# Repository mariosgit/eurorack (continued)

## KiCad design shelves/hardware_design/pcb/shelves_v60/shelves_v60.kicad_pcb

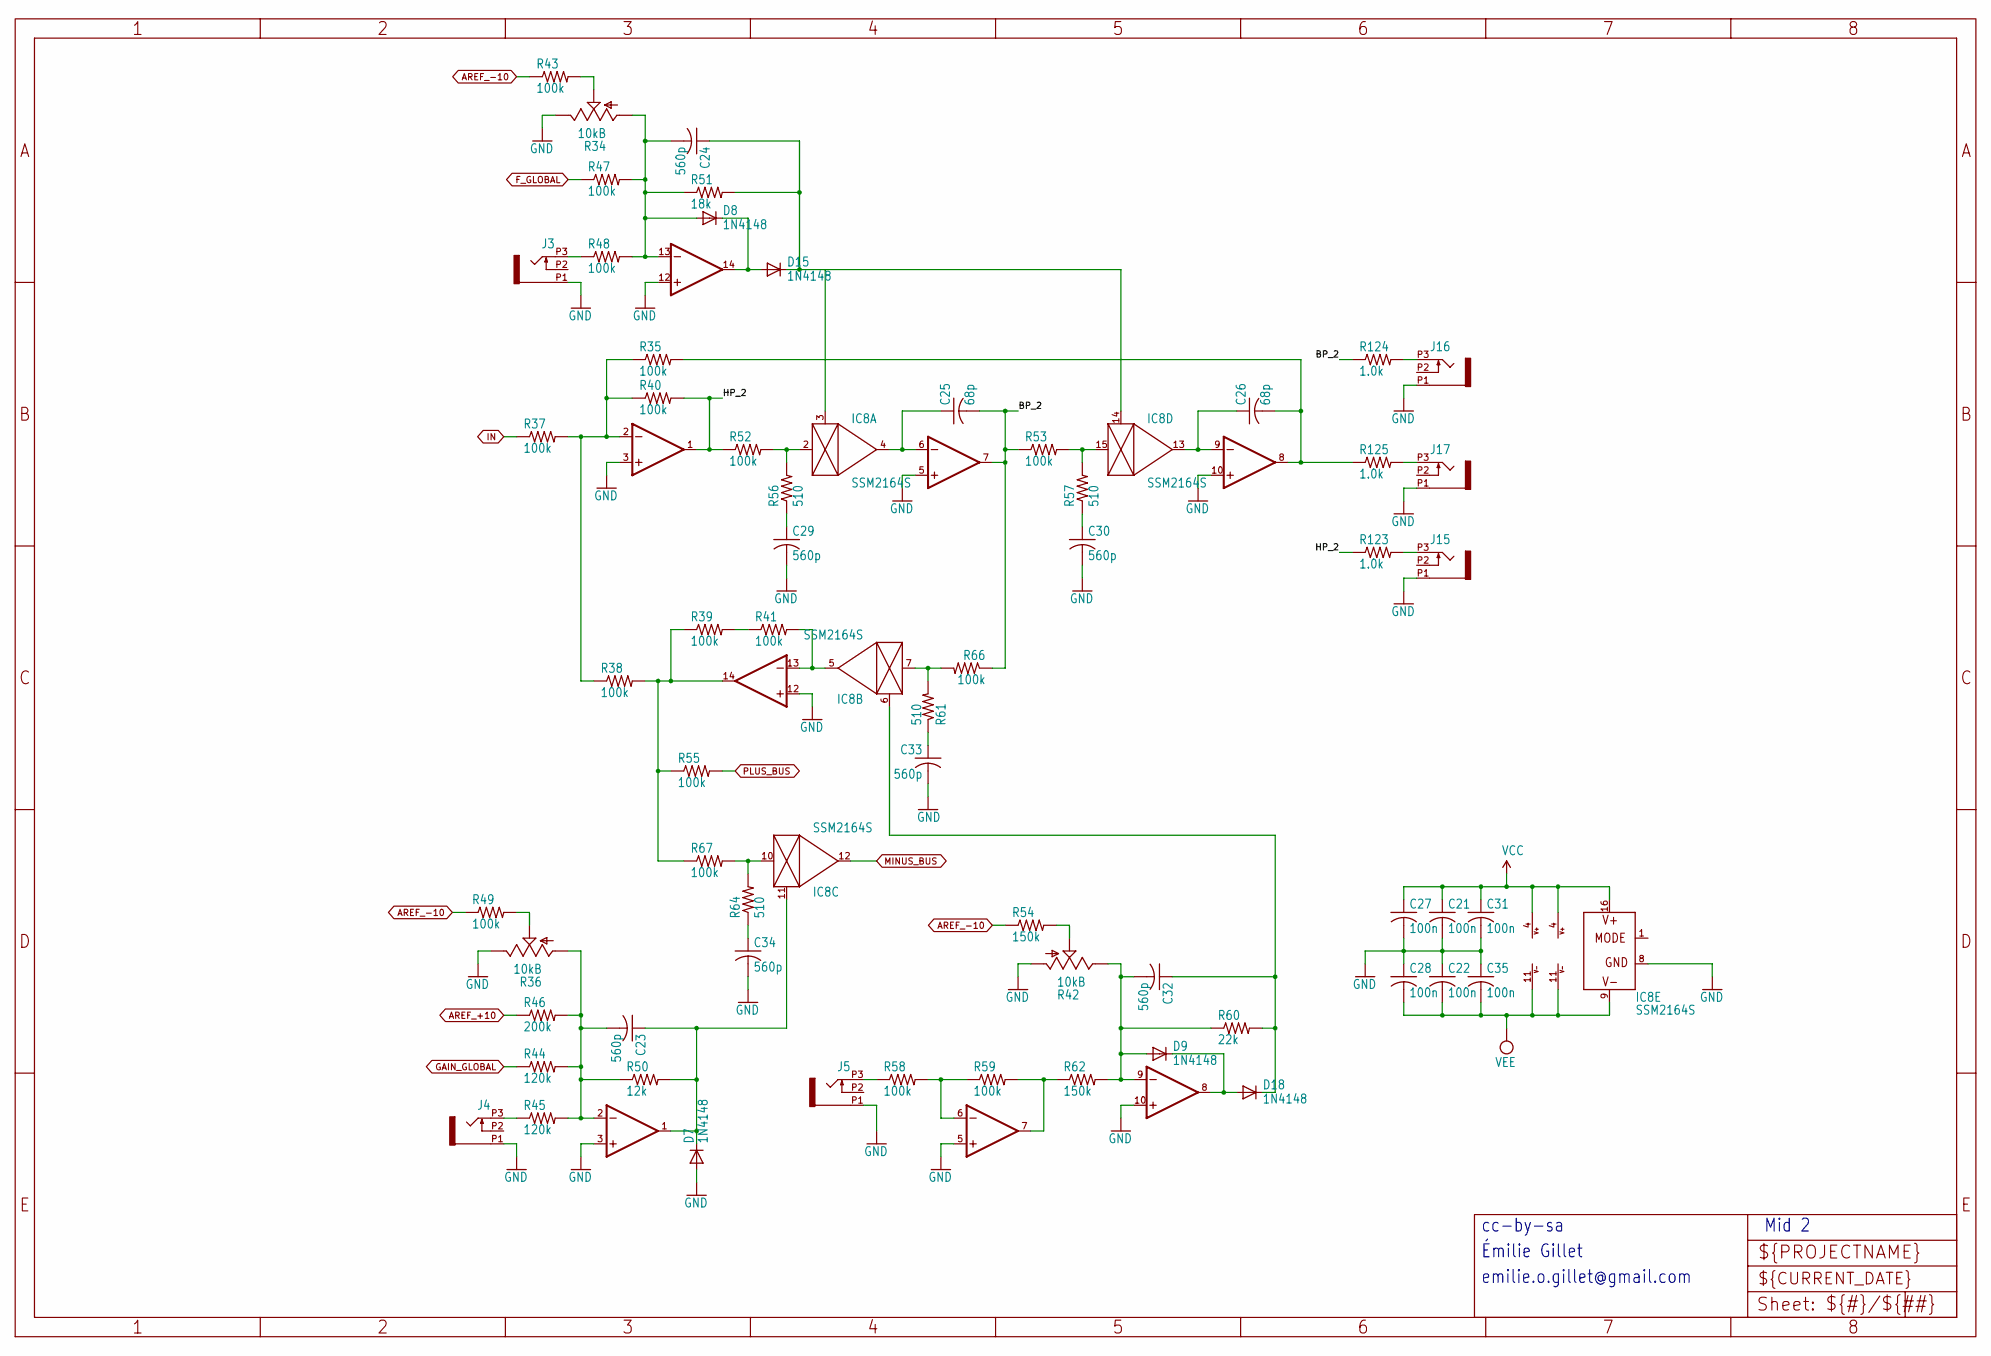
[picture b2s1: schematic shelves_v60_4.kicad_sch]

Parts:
C21, C22, C27, C28, C31, C35: 100n; C0603
C23, C24, C29, C30, C32, C33, C34: 560p; C0603
C25, C26: 68p; C0603
D7, D8, D9, D15, D18: 1N4148; SOD323-W
IC6, IC7: TL074D; SO14
IC8: SSM2164S; SOIC16N
J3, J4, J5, J15, J16, J17: PJ301_THONKICONN6; WQP_PJ_301M6
R34, R36: 10kB; ALPS_POT_VERTICAL_PS
R35, R37, R38, R39, R40, R41, R43, R47, R48, R49, R52, R53, R55, R58, R59, R66, R67: 100k; R0603
R42: 10kB; ALPS_POT_VERTICAL
R44, R45: 120k; R0603
R46: 200k; R0603
R50: 12k; R0603
R51: 18k; R0603
R54, R62: 150k; R0603
R56, R57, R61, R64: 510; R0603
R60: 22k; R0603
R123, R124, R125: 1.0k; R0603

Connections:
/shelves_v60_4/BP_2: C25.2, IC6.7 (OUT), R53.1, R66.1, R124.1
/shelves_v60_4/HP_2: IC6.1 (OUT), R40.2, R52.1, R123.1
AREF_+10: R46.1; also elsewhere on the board
AREF_-10: R43.1, R49.1, R54.1; also elsewhere on the board
F_GLOBAL: R47.1; also elsewhere on the board
GAIN_GLOBAL: R44.1; also elsewhere on the board
GND: C21.2, C22.1, C27.2, C28.1, C29.2, C30.2, C31.2, C33.2, C34.2, C35.1, D7.A, IC6.3 (+IN), IC6.5 (+IN), IC6.10 (+IN), IC6.12 (+IN), IC7.3 (+IN), IC7.5 (+IN), IC7.10 (+IN), IC7.12 (+IN), IC8.8 (GND), J3.P1 (1), J4.P1 (1), J5.P1 (1), J15.P1 (1), J16.P1 (1), J17.P1 (1), R34.P$1 (E), R36.P$1 (E), R42.P$3 (A); also elsewhere on the board
IN: R37.1; also elsewhere on the board
MINUS_BUS: IC8.12 (OUT); also elsewhere on the board
unnamed: C29.1, R56.1
unnamed: C30.1, R57.1
unnamed: C33.1, R61.1
unnamed: C34.1, R64.1
unnamed: IC6.2 (-IN), R35.1, R37.2, R38.1, R40.1
unnamed: C25.1, IC6.6 (-IN), IC8.4 (OUT)
unnamed: C26.1, IC6.9 (-IN), IC8.13 (OUT)
unnamed: C26.2, IC6.8 (OUT), R35.2, R125.1
unnamed: IC6.13 (-IN), IC8.5 (OUT), R41.2
unnamed: IC6.14 (OUT), R38.2, R39.1, R55.1, R67.1
unnamed: C23.2, IC7.2 (-IN), R36.P$3 (A), R44.2, R45.2, R46.2, R50.1
unnamed: C23.1, D7.C, IC7.1 (OUT), IC8.11 (CTRL), R50.2
unnamed: IC7.6 (-IN), R58.2, R59.1
unnamed: IC7.7 (OUT), R59.2, R62.1
unnamed: C32.2, D9.A, IC7.9 (-IN), R42.P$1 (E), R60.1, R62.2
unnamed: D9.C, D18.A, IC7.8 (OUT)
unnamed: C24.2, D8.A, IC7.13 (-IN), R34.P$3 (A), R47.2, R48.2, R51.1
unnamed: D8.C, D15.A, IC7.14 (OUT)
unnamed: C24.1, D15.C, IC8.3 (CTRL), IC8.14 (CTRL), R51.2
unnamed: IC8.2 (IN), R52.2, R56.2
unnamed: C32.1, D18.C, IC8.6 (CTRL), R60.2
unnamed: IC8.7 (IN), R61.2, R66.2
unnamed: IC8.10 (IN), R64.2, R67.2
unnamed: IC8.15 (IN), R53.2, R57.2
unnamed: J3.P3 (3), R48.1
unnamed: J4.P3 (3), R45.1
unnamed: J5.P3 (3), R58.1
unnamed: J15.P3 (3), R123.2
unnamed: J16.P3 (3), R124.2
unnamed: J17.P3 (3), R125.2
unnamed: R34.P$2 (S), R43.2
unnamed: R36.P$2 (S), R49.2
unnamed: R39.2, R41.1
unnamed: R42.P$2 (S), R54.2
PLUS_BUS: R55.2; also elsewhere on the board
VCC: C21.1, C27.1, C31.1, IC6.4 (V+), IC7.4 (V+), IC8.16 (V+); also elsewhere on the board
VEE: C22.2, C28.2, C35.2, IC6.11 (V-), IC7.11 (V-), IC8.9 (V-); also elsewhere on the board

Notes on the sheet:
Émilie Gillet
cc-by-sa
Mid 2
emilie.o.gillet@gmail.com

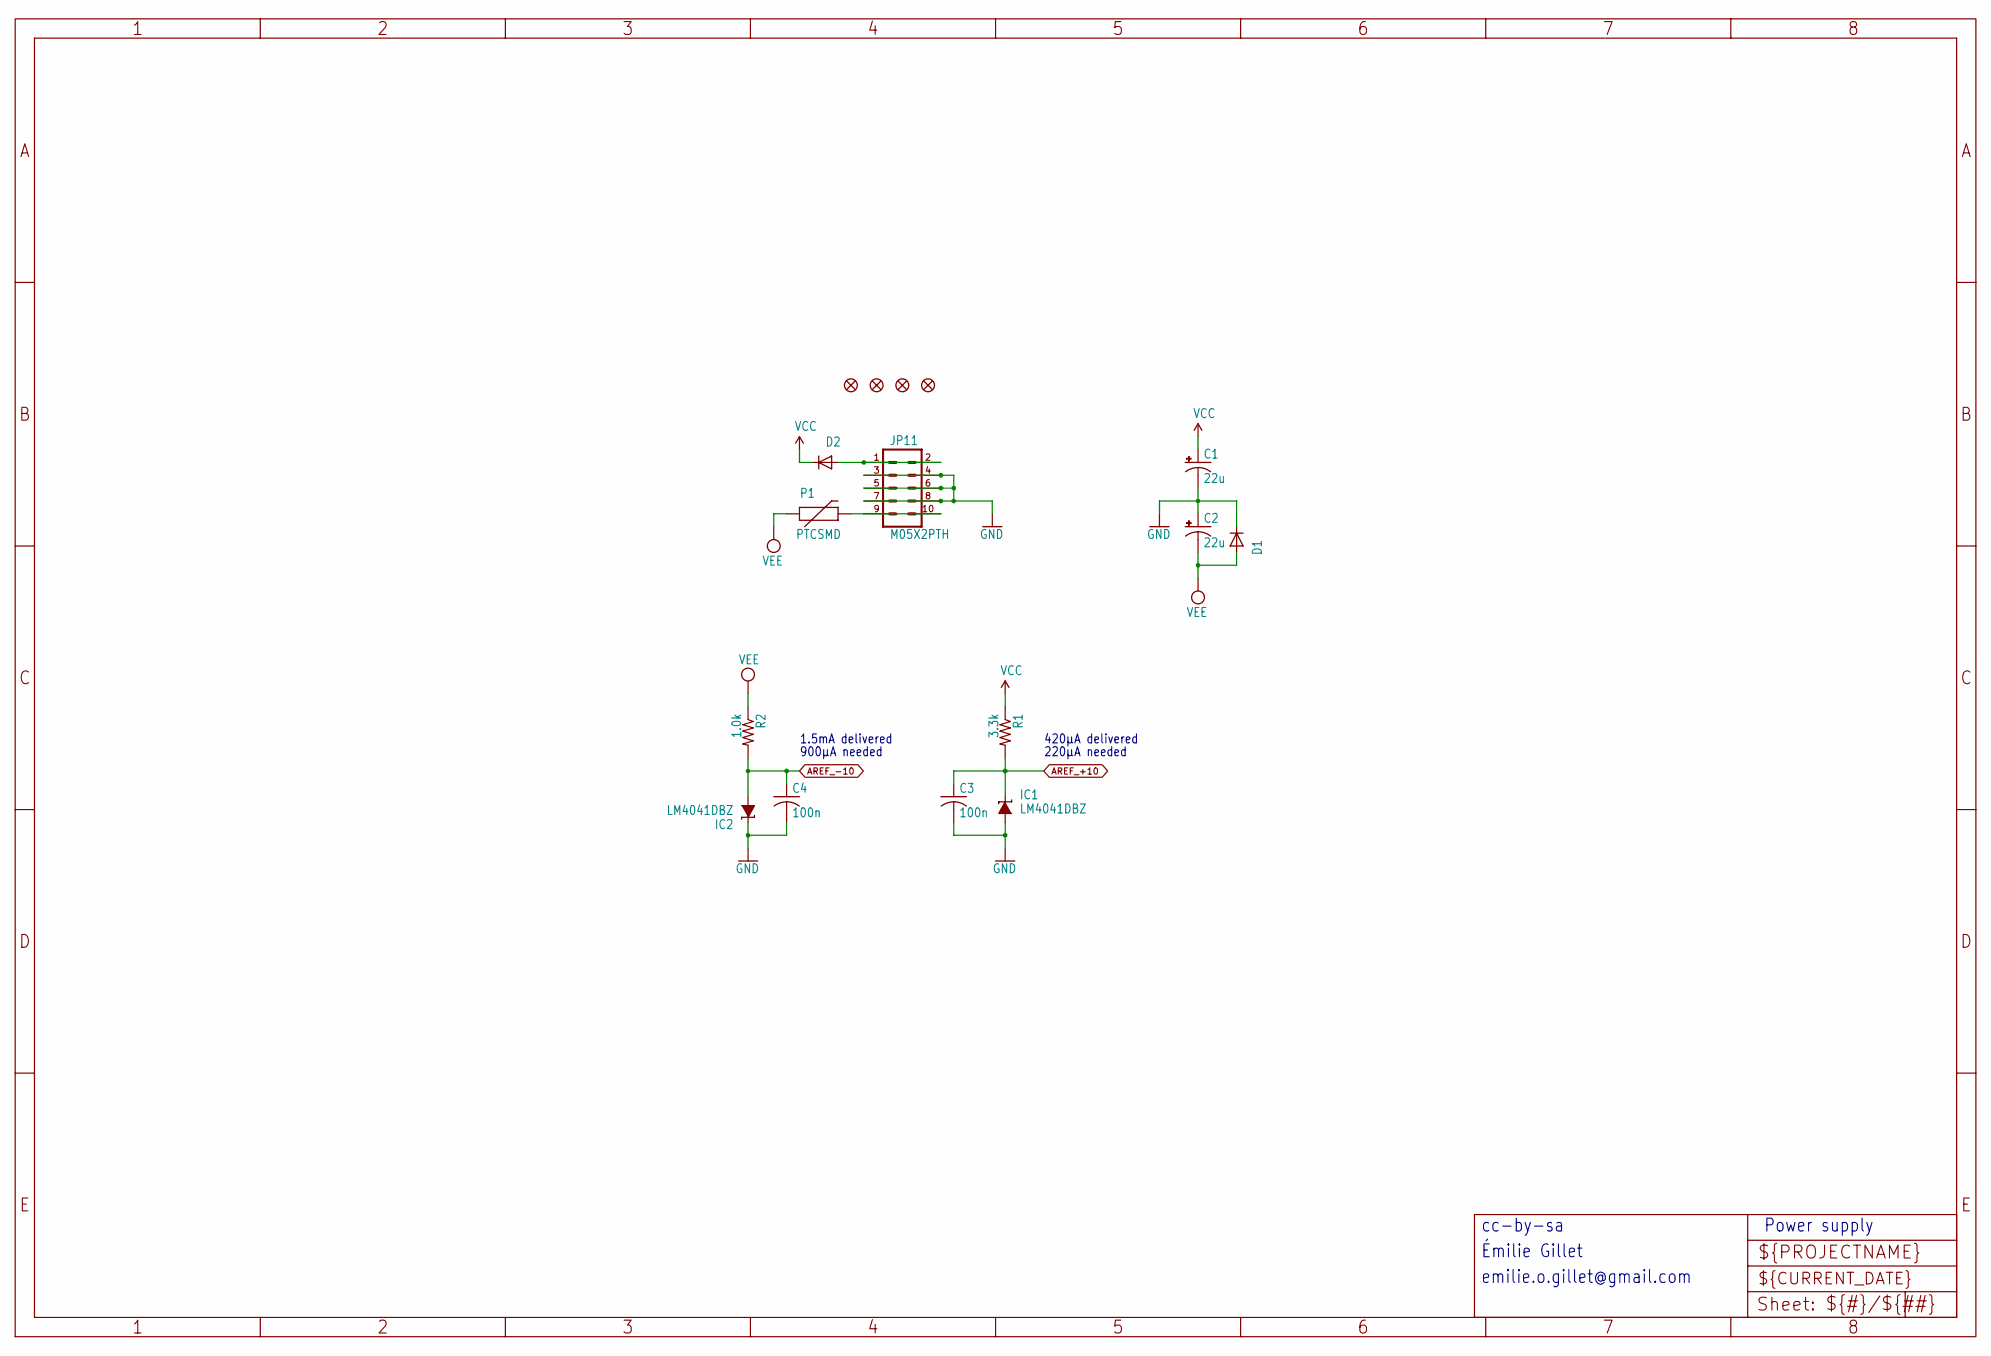
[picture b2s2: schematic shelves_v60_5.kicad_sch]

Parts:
C1, C2: 22u; PANASONIC_C
C3, C4: 100n; C0603
D1, D2: 1N5819HW; SOD123
IC1, IC2: LM4041DBZ; DBZ_R-PDSO-G3
JP1, JP2, JP3, JP4: FIDUCIAL1X2; FIDUCIAL-1X2
JP11: M05X2PTH; AVR_ICSP
P1: PTCSMD; PTC-1206
R1: 3.3k; R0603
R2: 1.0k; R0603

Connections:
AREF_+10: C3.1, IC1.1 (C), R1.2; also elsewhere on the board
AREF_-10: C4.1, IC2.2 (A), R2.2; also elsewhere on the board
GND: C1.-, C2.+, C3.2, C4.2, D1.C, IC1.2 (A), IC2.1 (C), JP11.3, JP11.4, JP11.5, JP11.6, JP11.7, JP11.8; also elsewhere on the board
unnamed: D2.A, JP11.1, JP11.2
unnamed: JP11.9, JP11.10, P1.2
VCC: C1.+, D2.C, R1.1; also elsewhere on the board
VEE: C2.-, D1.A, P1.1, R2.1; also elsewhere on the board

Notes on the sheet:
220µA needed
900µA needed
1.5mA delivered
cc-by-sa
emilie.o.gillet@gmail.com
420µA delivered
Power supply
Émilie Gillet

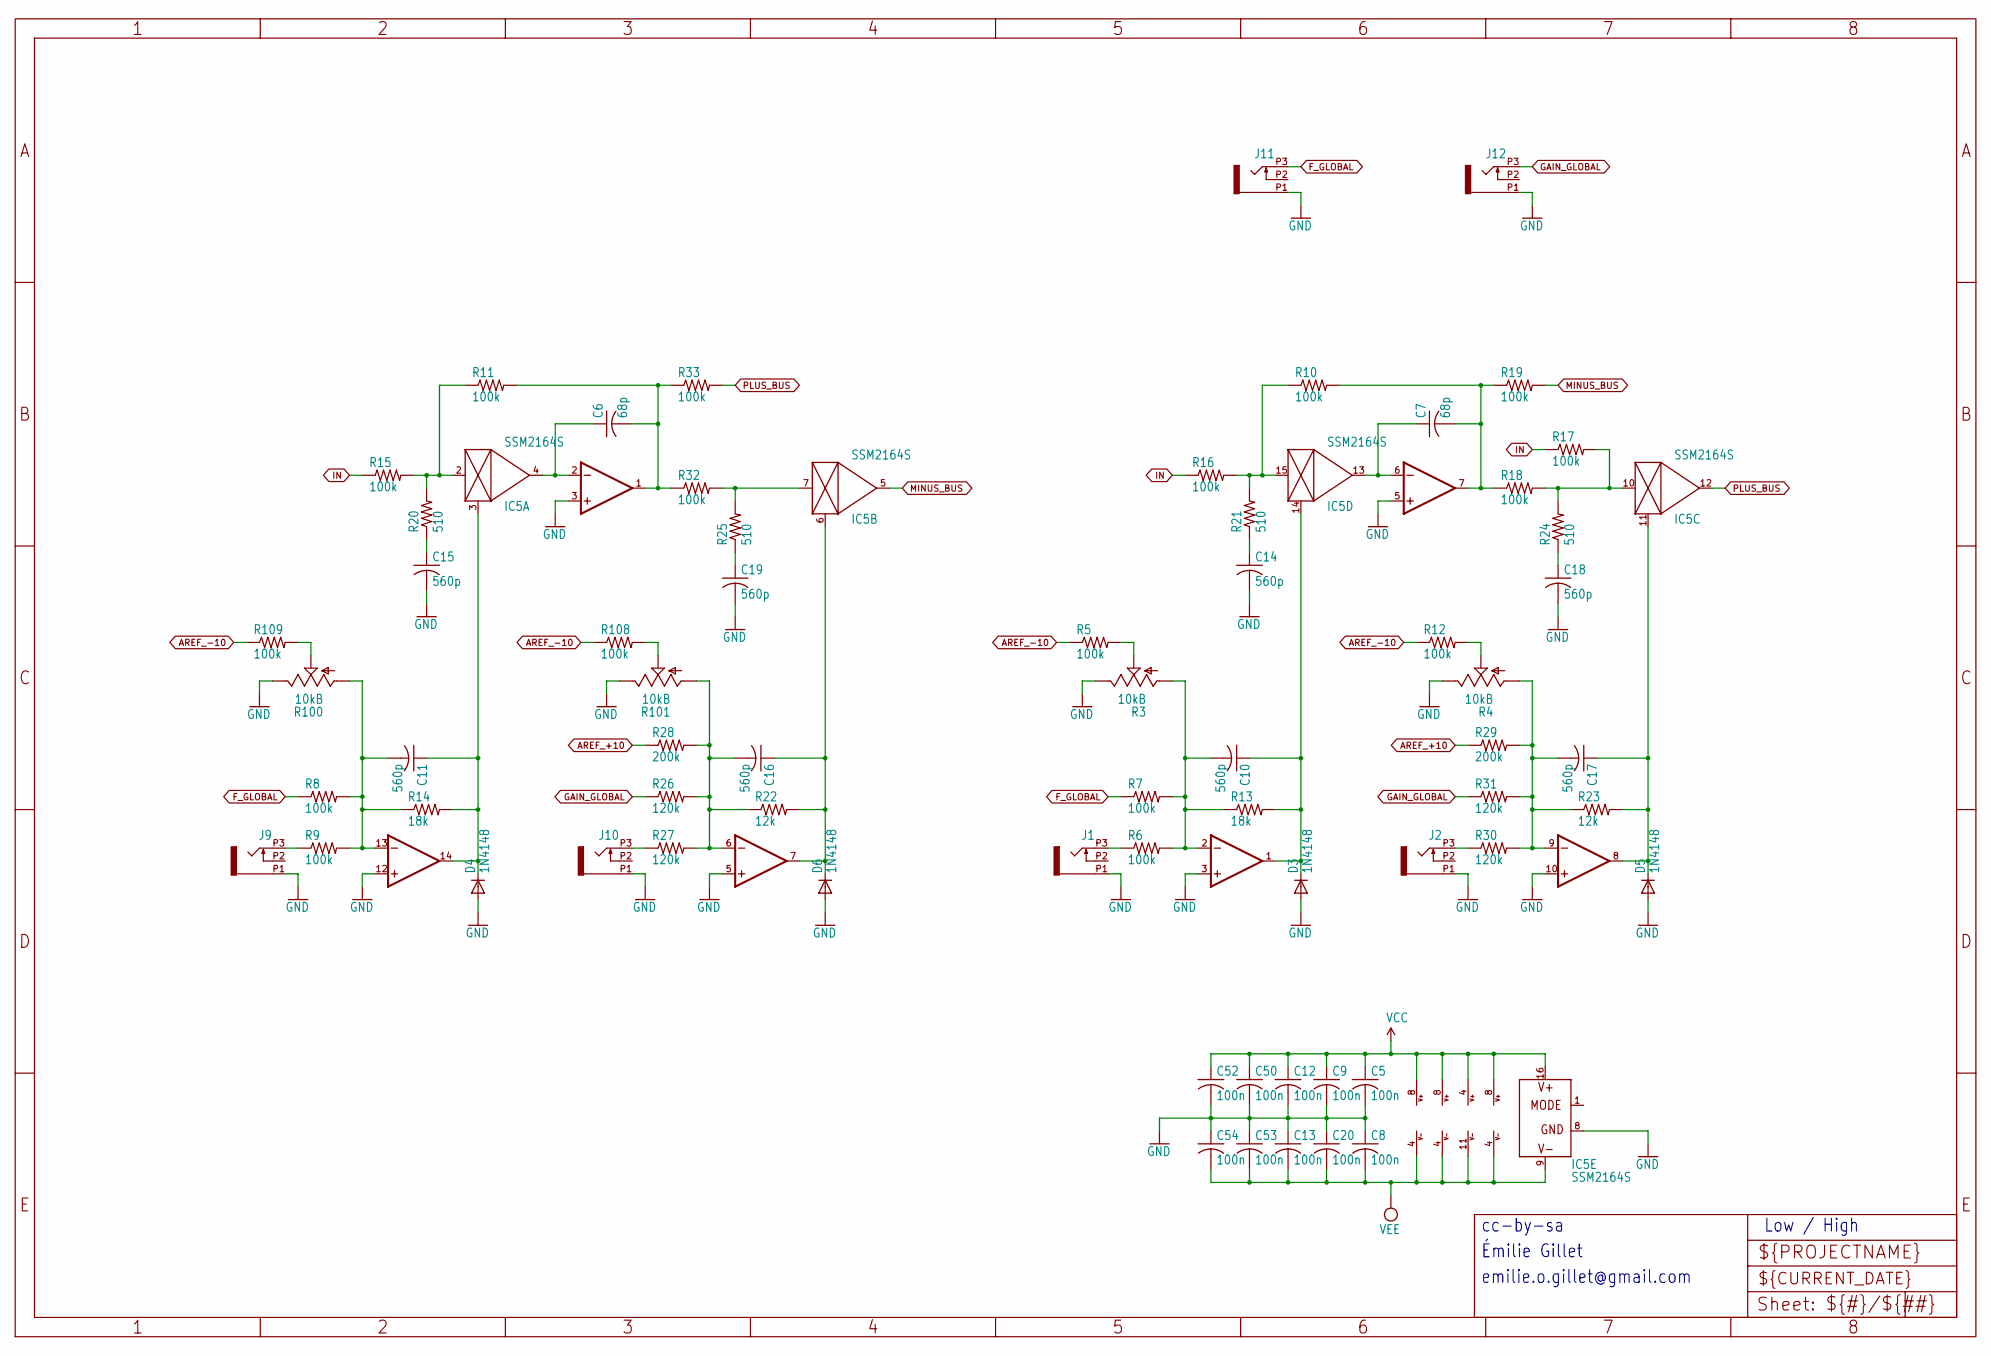
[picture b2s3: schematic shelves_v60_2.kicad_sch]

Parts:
C5, C8, C9, C12, C13, C20, C50, C52, C53, C54: 100n; C0603
C6, C7: 68p; C0603
C10, C11, C14, C15, C16, C17, C18, C19: 560p; C0603
D3, D4, D5, D6: 1N4148; SOD323-W
IC3, IC12, IC13: TL072D; SO08
IC4: TL074D; SO14
IC5: SSM2164S; SOIC16N
J1, J2, J9, J10, J11, J12: PJ301_THONKICONN6; WQP_PJ_301M6
R3, R4, R100, R101: 10kB; ALPS_POT_VERTICAL_PS
R5, R6, R7, R8, R9, R10, R11, R12, R15, R16, R17, R18, R19, R32, R33, R108, R109: 100k; R0603
R13, R14: 18k; R0603
R20, R21, R24, R25: 510; R0603
R22, R23: 12k; R0603
R26, R27, R30, R31: 120k; R0603
R28, R29: 200k; R0603

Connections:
AREF_+10: R28.1, R29.1; also elsewhere on the board
AREF_-10: R5.1, R12.1, R108.1, R109.1; also elsewhere on the board
F_GLOBAL: J11.P3 (3), R7.1, R8.1; also elsewhere on the board
GAIN_GLOBAL: J12.P3 (3), R26.1, R31.1; also elsewhere on the board
GND: C5.2, C8.1, C9.2, C12.2, C13.1, C14.2, C15.2, C18.2, C19.2, C20.1, C50.2, C52.2, C53.1, C54.1, D3.A, D4.A, D5.A, D6.A, IC3.3 (+IN), IC3.5 (+IN), IC4.3 (+IN), IC4.5 (+IN), IC4.10 (+IN), IC4.12 (+IN), IC5.8 (GND), J1.P1 (1), J2.P1 (1), J9.P1 (1), J10.P1 (1), J11.P1 (1), J12.P1 (1), R3.P$1 (E), R4.P$1 (E), R100.P$1 (E), R101.P$1 (E); also elsewhere on the board
IN: R15.1, R16.1, R17.1; also elsewhere on the board
MINUS_BUS: IC5.5 (OUT), R19.2; also elsewhere on the board
unnamed: C14.1, R21.1
unnamed: C15.1, R20.1
unnamed: C18.1, R24.1
unnamed: C19.1, R25.1
unnamed: C6.1, IC3.2 (-IN), IC5.4 (OUT)
unnamed: C6.2, IC3.1 (OUT), R11.2, R32.1, R33.1
unnamed: C7.1, IC3.6 (-IN), IC5.13 (OUT)
unnamed: C7.2, IC3.7 (OUT), R10.2, R18.1, R19.1
unnamed: C10.2, IC4.2 (-IN), R3.P$3 (A), R6.2, R7.2, R13.1
unnamed: C10.1, D3.C, IC4.1 (OUT), IC5.14 (CTRL), R13.2
unnamed: C16.2, IC4.6 (-IN), R22.1, R26.2, R27.2, R28.2, R101.P$3 (A)
unnamed: C16.1, D6.C, IC4.7 (OUT), IC5.6 (CTRL), R22.2
unnamed: C17.2, IC4.9 (-IN), R4.P$3 (A), R23.1, R29.2, R30.2, R31.2
unnamed: C17.1, D5.C, IC4.8 (OUT), IC5.11 (CTRL), R23.2
unnamed: C11.2, IC4.13 (-IN), R8.2, R9.2, R14.1, R100.P$3 (A)
unnamed: C11.1, D4.C, IC4.14 (OUT), IC5.3 (CTRL), R14.2
unnamed: IC5.2 (IN), R11.1, R15.2, R20.2
unnamed: IC5.7 (IN), R25.2, R32.2
unnamed: IC5.10 (IN), R17.2, R18.2, R24.2
unnamed: IC5.15 (IN), R10.1, R16.2, R21.2
unnamed: J1.P3 (3), R6.1
unnamed: J2.P3 (3), R30.1
unnamed: J9.P3 (3), R9.1
unnamed: J10.P3 (3), R27.1
unnamed: R3.P$2 (S), R5.2
unnamed: R4.P$2 (S), R12.2
unnamed: R100.P$2 (S), R109.2
unnamed: R101.P$2 (S), R108.2
PLUS_BUS: IC5.12 (OUT), R33.2; also elsewhere on the board
VCC: C5.1, C9.1, C12.1, C50.1, C52.1, IC3.8 (V+), IC4.4 (V+), IC5.16 (V+), IC12.8 (V+), IC13.8 (V+); also elsewhere on the board
VEE: C8.2, C13.2, C20.2, C53.2, C54.2, IC3.4 (V-), IC4.11 (V-), IC5.9 (V-), IC12.4 (V-), IC13.4 (V-); also elsewhere on the board

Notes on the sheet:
emilie.o.gillet@gmail.com
cc-by-sa
Émilie Gillet
Low / High

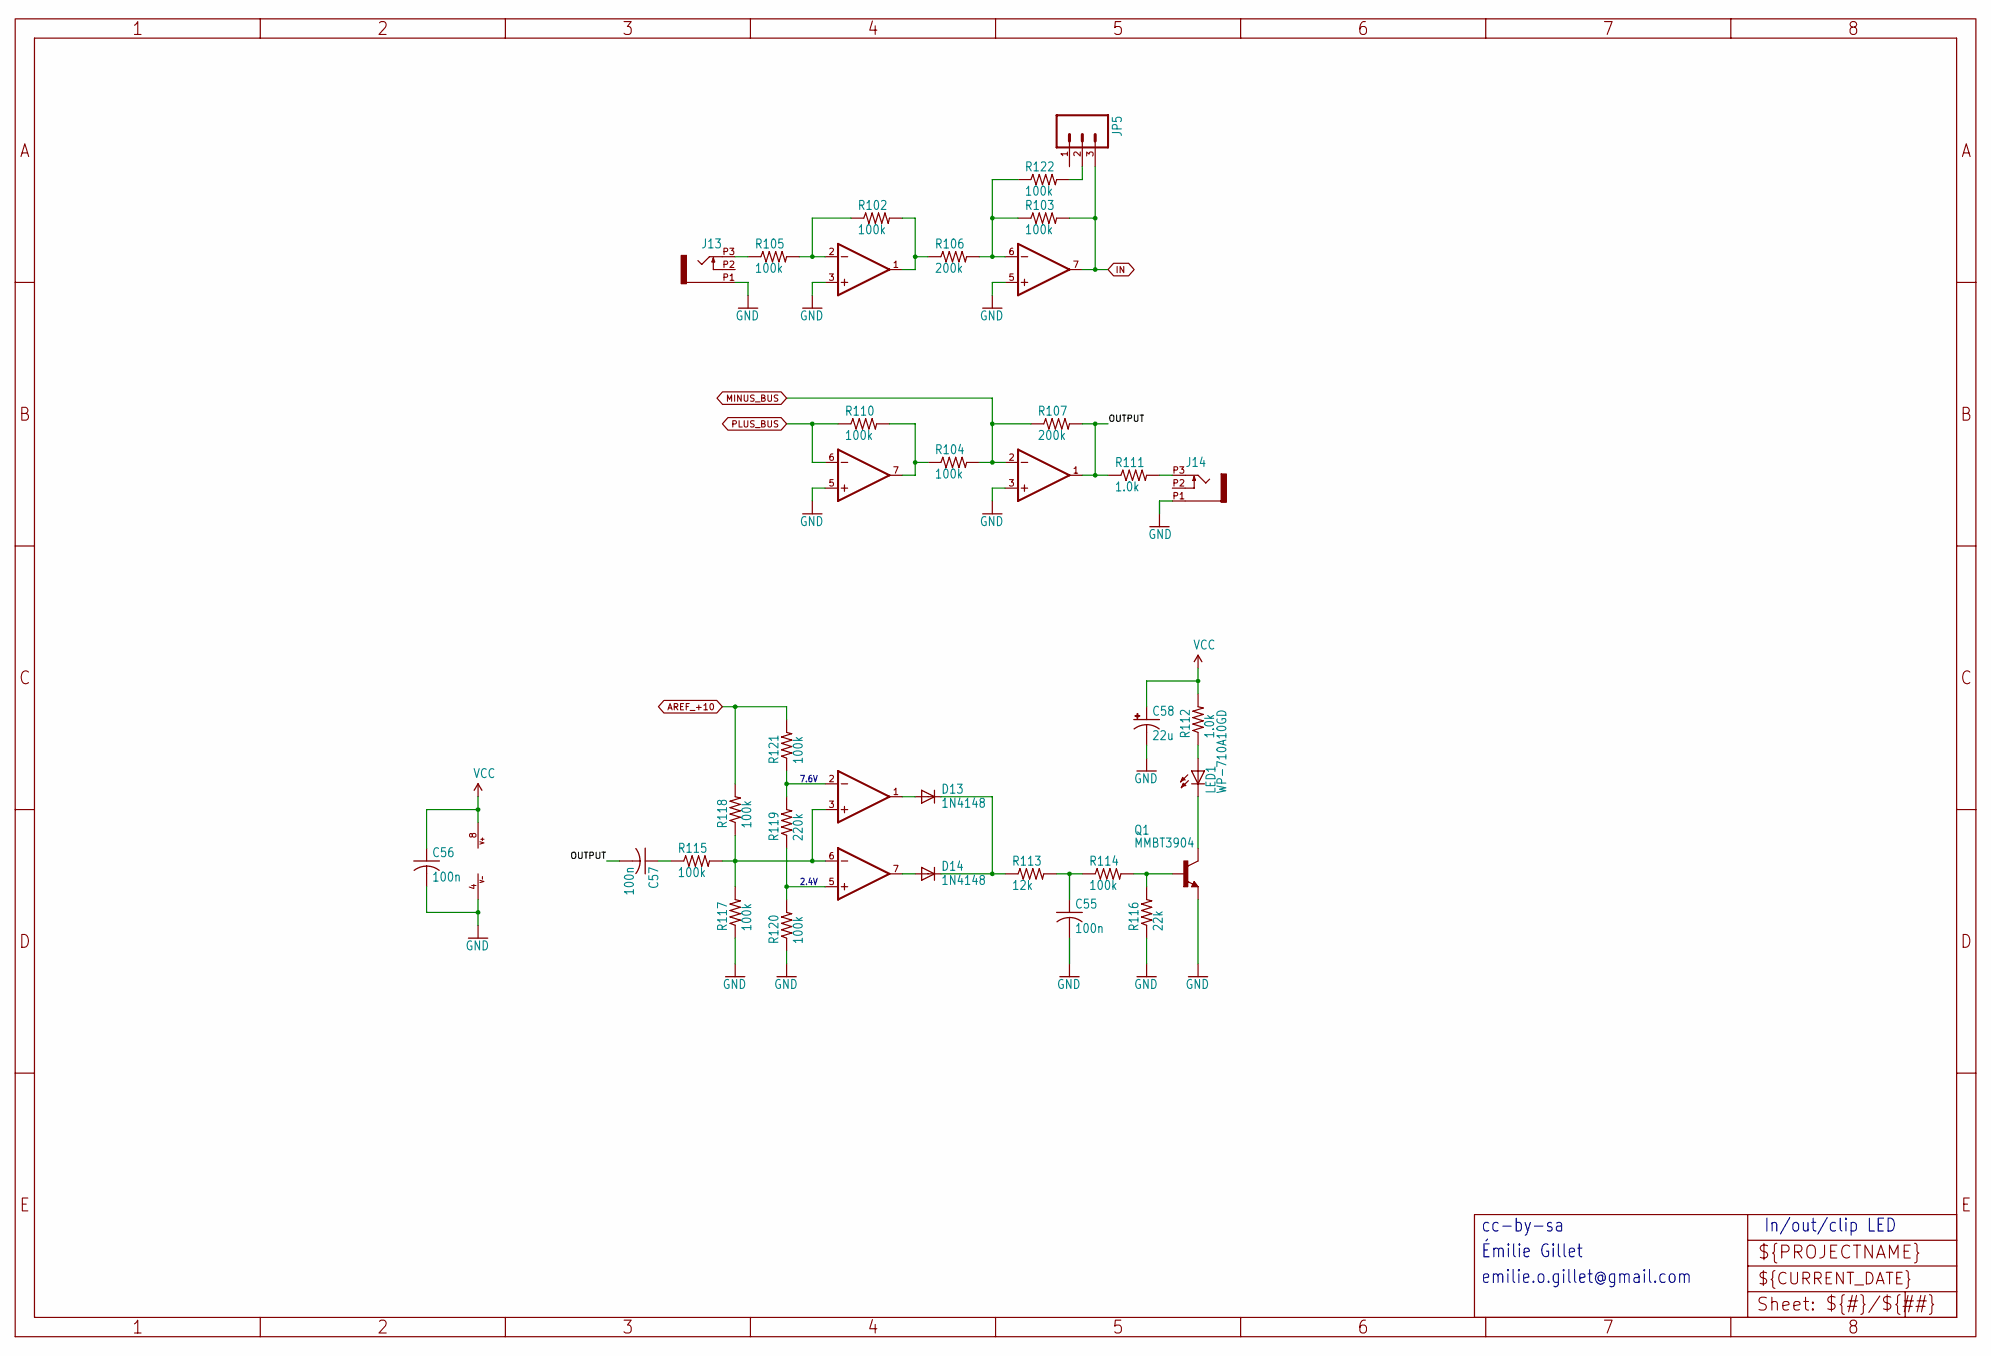
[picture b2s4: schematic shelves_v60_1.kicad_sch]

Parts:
C55, C56, C57: 100n; C0603
C58: 22u; PANASONIC_C
D13, D14: 1N4148; SOD323-W
IC12, IC13, IC14: TL072D; SO08
J13, J14: PJ301_THONKICONN6; WQP_PJ_301M6
JP5: M03PTH; 1X03
LED1: WP-710A10GD; LED3MM
Q1: MMBT3904; SOT23-BEC
R102, R103, R104, R105, R110, R114, R115, R117, R118, R120, R121, R122: 100k; R0603
R106, R107: 200k; R0603
R111, R112: 1.0k; R0603
R113: 12k; R0603
R116: 22k; R0603
R119: 220k; R0603

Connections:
/shelves_v60_1/OUTPUT: C57.2, IC13.1 (OUT), R107.2, R111.1
AREF_+10: R118.2, R121.2; also elsewhere on the board
GND: C55.2, C56.2, C58.-, IC12.3 (+IN), IC12.5 (+IN), IC13.3 (+IN), IC13.5 (+IN), IC14.4 (V-), J13.P1 (1), J14.P1 (1), Q1.E, R116.1, R117.1, R120.1; also elsewhere on the board
IN: IC12.7 (OUT), JP5.3, R103.2; also elsewhere on the board
MINUS_BUS: IC13.2 (-IN), R104.2, R107.1; also elsewhere on the board
unnamed: C55.1, R113.2, R114.1
unnamed: C57.1, R115.1
unnamed: D13.C, D14.C, R113.1
unnamed: IC12.2 (-IN), R102.1, R105.2
unnamed: IC12.1 (OUT), R102.2, R106.1
unnamed: IC12.6 (-IN), R103.1, R106.2, R122.1
unnamed: IC13.7 (OUT), R104.1, R110.2
unnamed: IC14.3 (+IN), IC14.6 (-IN), R115.2, R117.2, R118.1
unnamed: IC14.2 (-IN), R119.2, R121.1
unnamed: D13.A, IC14.1 (OUT)
unnamed: IC14.5 (+IN), R119.1, R120.2
unnamed: D14.A, IC14.7 (OUT)
unnamed: J13.P3 (3), R105.1
unnamed: J14.P3 (3), R111.2
unnamed: JP5.2, R122.2
unnamed: LED1.K (C), Q1.C
unnamed: LED1.A, R112.1
unnamed: Q1.B, R114.2, R116.2
PLUS_BUS: IC13.6 (-IN), R110.1; also elsewhere on the board
VCC: C56.1, C58.+, IC14.8 (V+), R112.2; also elsewhere on the board

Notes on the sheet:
7.6V
2.4V
Émilie Gillet
In/out/clip LED
cc-by-sa
emilie.o.gillet@gmail.com

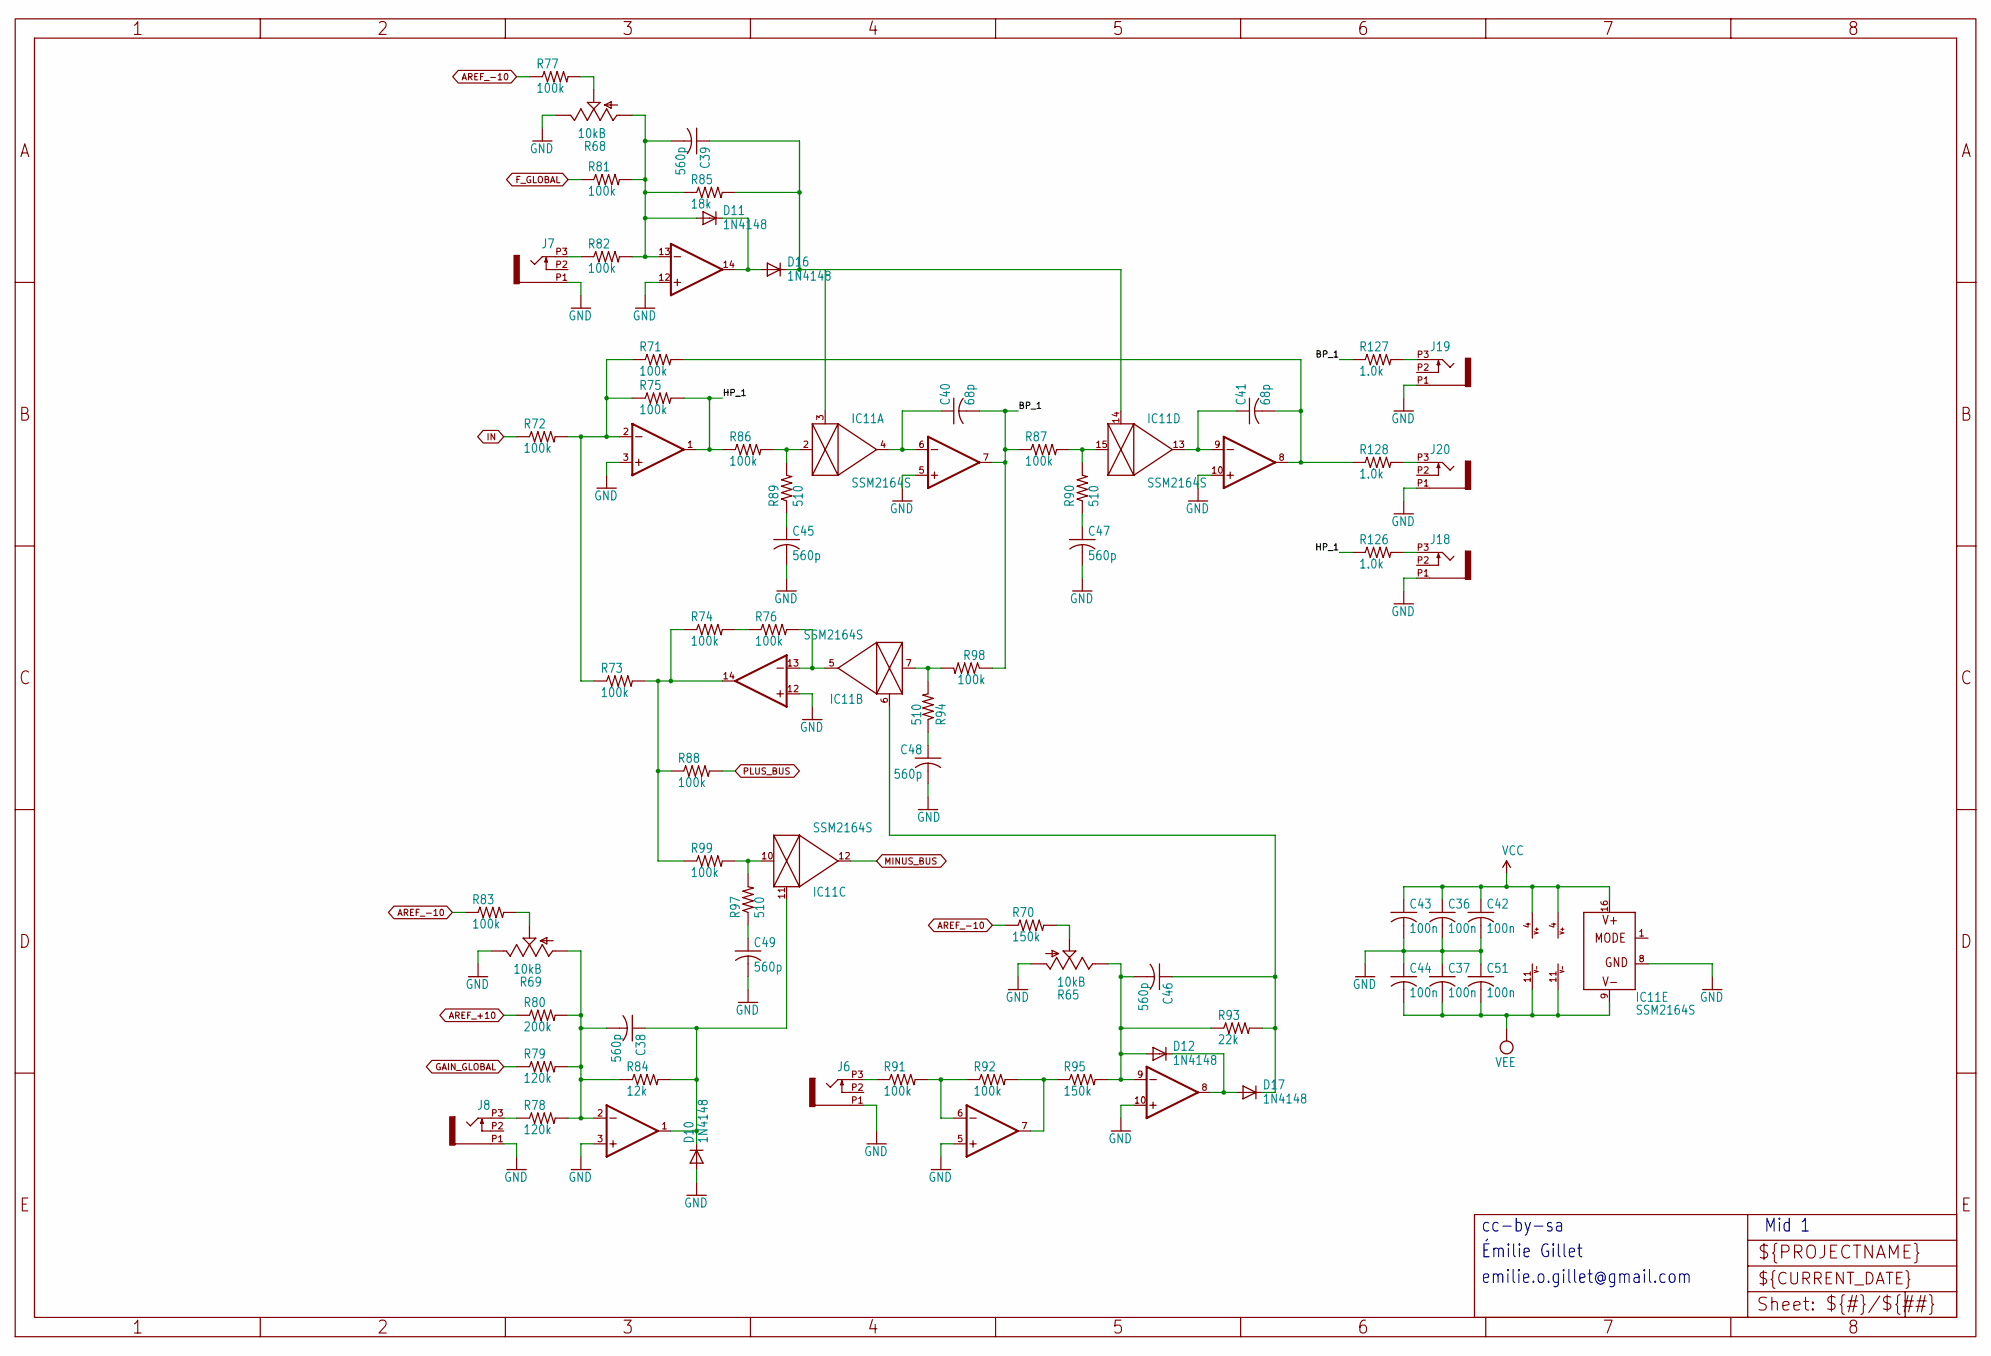
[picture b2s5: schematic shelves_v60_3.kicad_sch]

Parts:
C36, C37, C42, C43, C44, C51: 100n; C0603
C38, C39, C45, C46, C47, C48, C49: 560p; C0603
C40, C41: 68p; C0603
D10, D11, D12, D16, D17: 1N4148; SOD323-W
IC9, IC10: TL074D; SO14
IC11: SSM2164S; SOIC16N
J6, J7, J8, J18, J19, J20: PJ301_THONKICONN6; WQP_PJ_301M6
R65: 10kB; ALPS_POT_VERTICAL
R68, R69: 10kB; ALPS_POT_VERTICAL_PS
R70, R95: 150k; R0603
R71, R72, R73, R74, R75, R76, R77, R81, R82, R83, R86, R87, R88, R91, R92, R98, R99: 100k; R0603
R78, R79: 120k; R0603
R80: 200k; R0603
R84: 12k; R0603
R85: 18k; R0603
R89, R90, R94, R97: 510; R0603
R93: 22k; R0603
R126, R127, R128: 1.0k; R0603

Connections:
/shelves_v60_3/BP_1: C40.2, IC9.7 (OUT), R87.1, R98.1, R127.1
/shelves_v60_3/HP_1: IC9.1 (OUT), R75.2, R86.1, R126.1
AREF_+10: R80.1; also elsewhere on the board
AREF_-10: R70.1, R77.1, R83.1; also elsewhere on the board
F_GLOBAL: R81.1; also elsewhere on the board
GAIN_GLOBAL: R79.1; also elsewhere on the board
GND: C36.2, C37.1, C42.2, C43.2, C44.1, C45.2, C47.2, C48.2, C49.2, C51.1, D10.A, IC9.3 (+IN), IC9.5 (+IN), IC9.10 (+IN), IC9.12 (+IN), IC10.3 (+IN), IC10.5 (+IN), IC10.10 (+IN), IC10.12 (+IN), IC11.8 (GND), J6.P1 (1), J7.P1 (1), J8.P1 (1), J18.P1 (1), J19.P1 (1), J20.P1 (1), R65.P$3 (A), R68.P$1 (E), R69.P$1 (E); also elsewhere on the board
IN: R72.1; also elsewhere on the board
MINUS_BUS: IC11.12 (OUT); also elsewhere on the board
unnamed: C45.1, R89.1
unnamed: C47.1, R90.1
unnamed: C48.1, R94.1
unnamed: C49.1, R97.1
unnamed: IC9.2 (-IN), R71.1, R72.2, R73.1, R75.1
unnamed: C41.2, IC9.8 (OUT), R71.2, R128.1
unnamed: IC9.14 (OUT), R73.2, R74.1, R88.1, R99.1
unnamed: C38.2, IC10.2 (-IN), R69.P$3 (A), R78.2, R79.2, R80.2, R84.1
unnamed: C38.1, D10.C, IC10.1 (OUT), IC11.11 (CTRL), R84.2
unnamed: IC10.6 (-IN), R91.2, R92.1
unnamed: IC10.7 (OUT), R92.2, R95.1
unnamed: C46.2, D12.A, IC10.9 (-IN), R65.P$1 (E), R93.1, R95.2
unnamed: D12.C, D17.A, IC10.8 (OUT)
unnamed: C39.2, D11.A, IC10.13 (-IN), R68.P$3 (A), R81.2, R82.2, R85.1
unnamed: D11.C, D16.A, IC10.14 (OUT)
unnamed: C39.1, D16.C, IC11.3 (CTRL), IC11.14 (CTRL), R85.2
unnamed: IC11.2 (IN), R86.2, R89.2
unnamed: C40.1, IC9.6 (-IN), IC11.4 (OUT)
unnamed: C46.1, D17.C, IC11.6 (CTRL), R93.2
unnamed: IC11.7 (IN), R94.2, R98.2
unnamed: IC9.13 (-IN), IC11.5 (OUT), R76.2
unnamed: IC11.10 (IN), R97.2, R99.2
unnamed: IC11.15 (IN), R87.2, R90.2
unnamed: C41.1, IC9.9 (-IN), IC11.13 (OUT)
unnamed: J6.P3 (3), R91.1
unnamed: J7.P3 (3), R82.1
unnamed: J8.P3 (3), R78.1
unnamed: J18.P3 (3), R126.2
unnamed: J19.P3 (3), R127.2
unnamed: J20.P3 (3), R128.2
unnamed: R65.P$2 (S), R70.2
unnamed: R68.P$2 (S), R77.2
unnamed: R69.P$2 (S), R83.2
unnamed: R74.2, R76.1
PLUS_BUS: R88.2; also elsewhere on the board
VCC: C36.1, C42.1, C43.1, IC9.4 (V+), IC10.4 (V+), IC11.16 (V+); also elsewhere on the board
VEE: C37.2, C44.2, C51.2, IC9.11 (V-), IC10.11 (V-), IC11.9 (V-); also elsewhere on the board

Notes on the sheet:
Émilie Gillet
Mid 1
cc-by-sa
emilie.o.gillet@gmail.com
